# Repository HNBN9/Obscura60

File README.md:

# Obscura60
first keyboard build 60% wireless

Colored By -<br>
Mr.Finishing Surfacer 1500 Black<br>
Tamiya TS81 - top<br>
Tamiya TS55 - bottom<br>

Keycaps - 日当午GMK Prussian Alert普鲁(ordered 1 more 3u spacebar)<br>

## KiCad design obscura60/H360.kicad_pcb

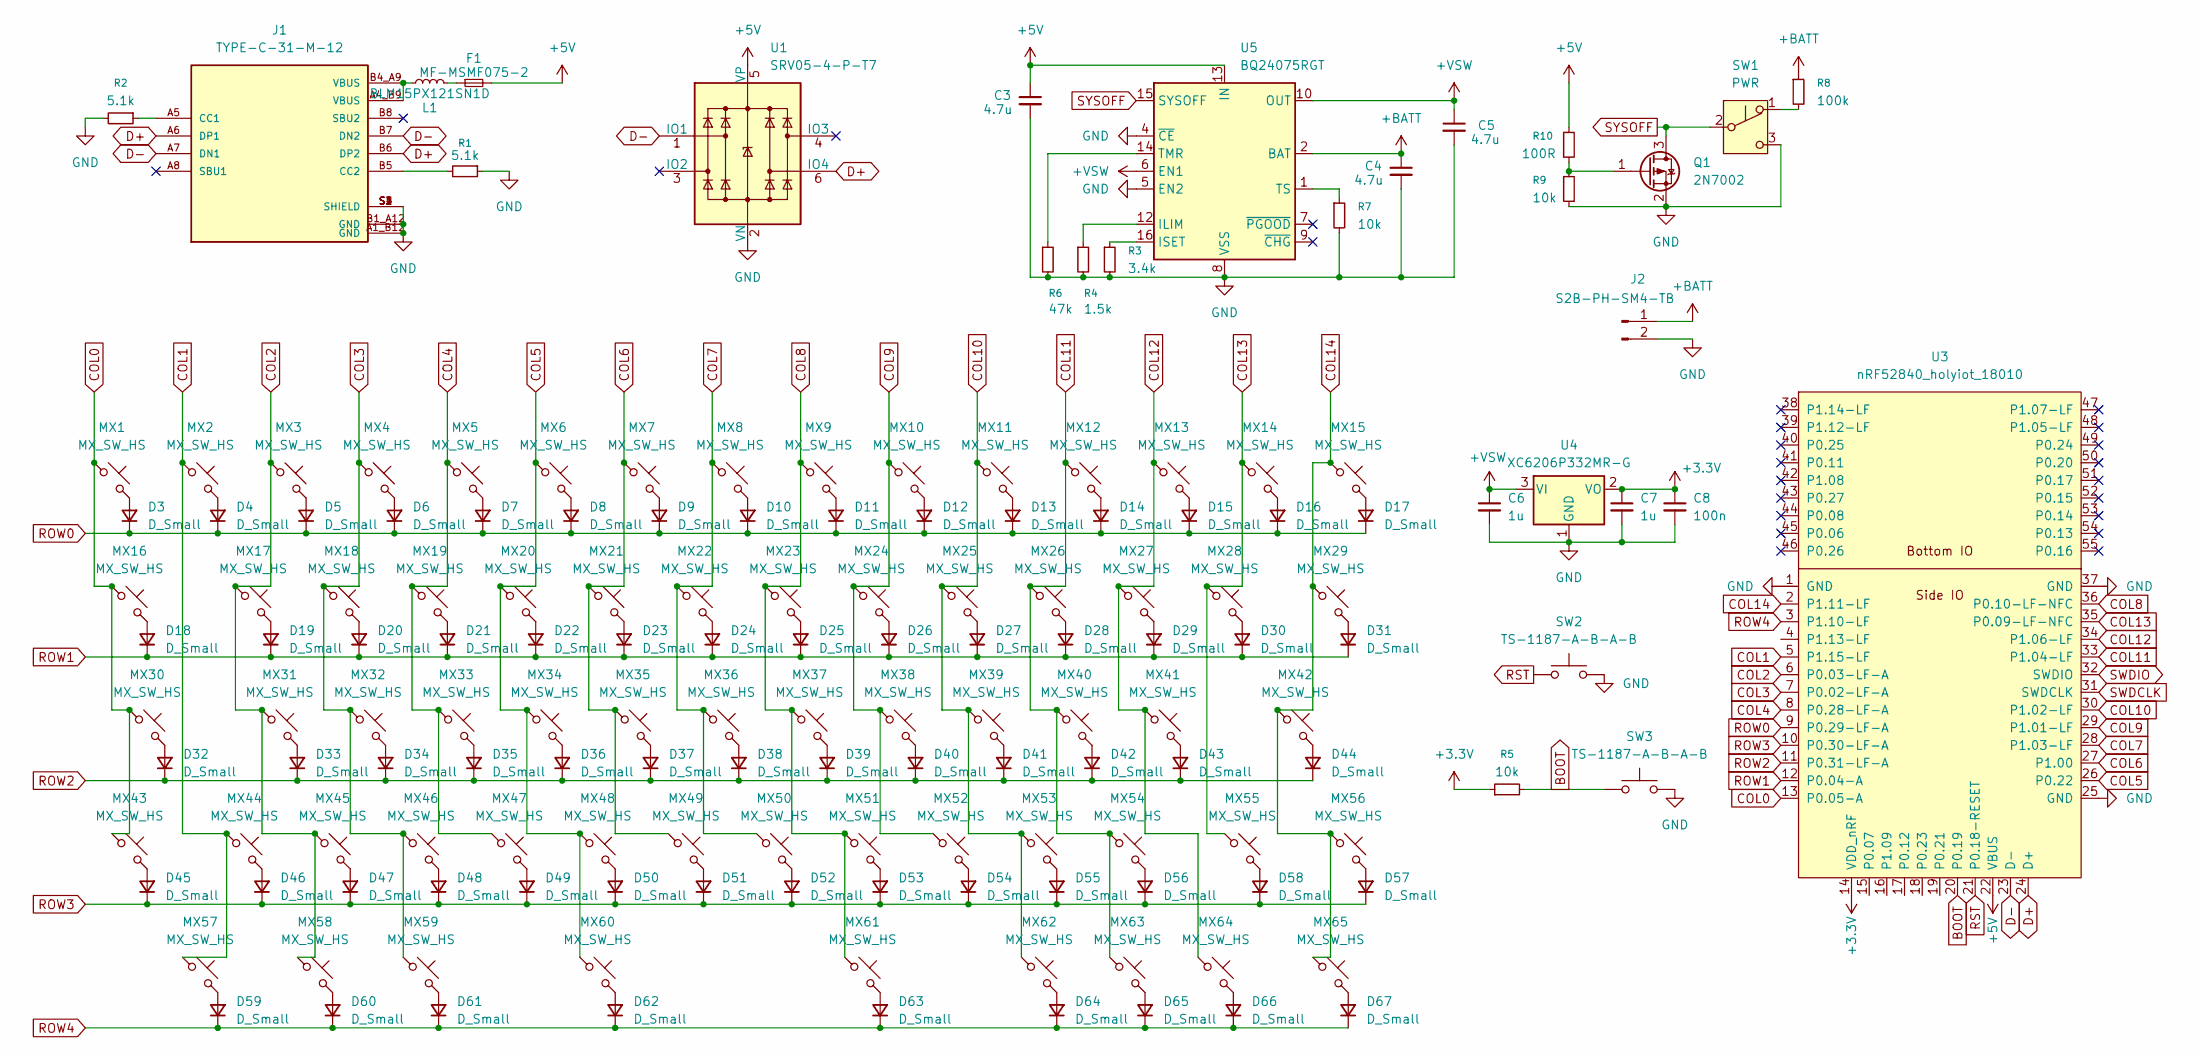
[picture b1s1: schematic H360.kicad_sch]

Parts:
C3, C4, C5: 4.7u; C_0603_1608Metric
C6, C7: 1u; C_1206_3216Metric
C8: 100n; C_0402_1005Metric
D3, D4, D5, D6, D7, D8, D9, D10, D11, D12, D13, D14, D15, D16, D17, D18, D19, D20, D21, D22, D23, D24, D25, D26, D27, D28, D29, D30, D31, D32, D33, D34, D35, D36, D37, D38, D39, D40, D41, D42, D43, D44, D45, D46, D47, D48, D49, D50, D51, D52, D53, D54, D55, D56, D57, D58, D59, D60, D61, D62, D63, D64, D65, D66, D67: D_Small; D_SOD-123
F1: MF-MSMF075-2; R_1812_4532Metric
J1: TYPE-C-31-M-12; HRO_TYPE-C-31-M-12; PARTREV 2020.12.08
J2: S2B-PH-SM4-TB; JST_PH_S2B-PH-SM4-TB_1x02-1MP_P2.00mm_Horizontal
L1: BLM15PX121SN1D; L_0402_1005Metric
MX1, MX2, MX3, MX4, MX5, MX6, MX7, MX8, MX9, MX10, MX11, MX12, MX13, MX14, MX15, MX16, MX17, MX18, MX19, MX20, MX21, MX22, MX23, MX24, MX25, MX26, MX27, MX28, MX29, MX30, MX31, MX32, MX33, MX34, MX35, MX36, MX37, MX38, MX39, MX40, MX41, MX42, MX43, MX44, MX45, MX46, MX47, MX48, MX49, MX50, MX51, MX52, MX53, MX54, MX55, MX56, MX57, MX58, MX59, MX60, MX61, MX62, MX63, MX64, MX65: MX_SW_HS; SW_MX_HS_CPG151101S11_1u
Q1: 2N7002; SOT-23
R1, R2: 5.1k; R_0402_1005Metric
R3: 3.4k; R_0603_1608Metric
R4: 1.5k; R_0402_1005Metric
R5, R7, R9: 10k; R_0402_1005Metric
R6: 47k; R_0402_1005Metric
R8: 100k; R_0402_1005Metric
R10: 100R; R_0402_1005Metric
SW1: PWR; SW_SPDT_CK_JS102011SAQN
SW2, SW3: TS-1187-A-B-A-B; SW_Push_1P1T_XKB_TS-1187A
U1: SRV05-4-P-T7; SOT-23-6
U3: nRF52840_holyiot_18010
U4: XC6206P332MR-G; SOT-23-3
U5: BQ24075RGT; VQFN-16-1EP_3x3mm_P0.5mm_EP1.6x1.6mm

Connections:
+3.3V: C7.1, C8.1, R5.1, U3.14 (VDD_nRF), U4.2 (VO)
+5V: C3.1, F1.2, R10.1, U1.5 (VP), U3.22 (VBUS), U5.13 (IN)
+BATT: C4.1, J2.1, R8.1, U5.2 (BAT), U5.3 (BAT)
+VSW: C5.1, C6.1, U4.3 (VI), U5.6 (EN1), U5.10 (OUT), U5.11 (OUT)
BOOT: R5.2, SW3.1, U3.20 (P0.19)
COL0: MX1.1, MX16.1, MX30.1, MX43.1, U3.13 (P0.05-A)
COL1: MX2.1, MX44.1, MX57.1, U3.5 (P1.15-LF)
COL2: MX3.1, MX17.1, MX31.1, MX45.1, MX58.1, U3.6 (P0.03-LF-A)
COL3: MX4.1, MX18.1, MX32.1, MX46.1, MX59.1, U3.7 (P0.02-LF-A)
COL4: MX5.1, MX19.1, MX33.1, MX47.1, U3.8 (P0.28-LF-A)
COL5: MX6.1, MX20.1, MX34.1, MX48.1, MX60.1, U3.26 (P0.22)
COL6: MX7.1, MX21.1, MX35.1, MX49.1, U3.27 (P1.00)
COL7: MX8.1, MX22.1, MX36.1, MX50.1, U3.28 (P1.03-LF)
COL8: MX9.1, MX23.1, MX37.1, MX51.1, MX61.1, U3.36 (P0.10-LF-NFC)
COL9: MX10.1, MX24.1, MX38.1, MX52.1, U3.29 (P1.01-LF)
COL10: MX11.1, MX25.1, MX39.1, MX53.1, MX62.1, U3.30 (P1.02-LF)
COL11: MX12.1, MX26.1, MX40.1, MX54.1, MX63.1, U3.33 (P1.04-LF)
COL12: MX13.1, MX27.1, MX41.1, MX64.1, U3.34 (P1.06-LF)
COL13: MX14.1, MX28.1, MX55.1, U3.35 (P0.09-LF-NFC)
COL14: MX15.1, MX29.1, MX42.1, MX56.1, MX65.1, U3.2 (P1.11-LF)
D+: J1.A6 (DP1), J1.B6 (DP2), U1.6 (IO4), U3.24 (D+)
D-: J1.A7 (DN1), J1.B7 (DN2), U1.1 (IO1), U3.23 (D-)
GND: C3.2, C4.2, C5.2, C6.2, C7.2, C8.2, J1.A1_B12 (GND), J1.B1_A12 (GND), J1.S1 (SHIELD), J1.S2 (SHIELD), J1.S3 (SHIELD), J1.S4 (SHIELD), J2.2, Q1.2 (S), R1.1, R2.2, R3.2, R4.2, R6.2, R7.2, R9.2, SW1.3 (C), SW2.2, SW3.2, U1.2 (VN), U3.1 (GND), U3.25 (GND), U3.37 (GND), U4.1 (GND), U5.4 (~CE), U5.5 (EN2), U5.8 (VSS), U5.17 (VSS)
unnamed: D3.2 (A), MX1.2
unnamed: D4.2 (A), MX2.2
unnamed: D5.2 (A), MX3.2
unnamed: D6.2 (A), MX4.2
unnamed: D7.2 (A), MX5.2
unnamed: D8.2 (A), MX6.2
unnamed: D9.2 (A), MX7.2
unnamed: D10.2 (A), MX8.2
unnamed: D11.2 (A), MX9.2
unnamed: D12.2 (A), MX10.2
unnamed: D13.2 (A), MX11.2
unnamed: D14.2 (A), MX12.2
unnamed: D15.2 (A), MX13.2
unnamed: D16.2 (A), MX14.2
unnamed: D17.2 (A), MX15.2
unnamed: D18.2 (A), MX16.2
unnamed: D19.2 (A), MX17.2
unnamed: D20.2 (A), MX18.2
unnamed: D21.2 (A), MX19.2
unnamed: D22.2 (A), MX20.2
unnamed: D23.2 (A), MX21.2
unnamed: D24.2 (A), MX22.2
unnamed: D25.2 (A), MX23.2
unnamed: D26.2 (A), MX24.2
unnamed: D27.2 (A), MX25.2
unnamed: D28.2 (A), MX26.2
unnamed: D29.2 (A), MX27.2
unnamed: D30.2 (A), MX28.2
unnamed: D31.2 (A), MX29.2
unnamed: D32.2 (A), MX30.2
unnamed: D33.2 (A), MX31.2
unnamed: D34.2 (A), MX32.2
unnamed: D35.2 (A), MX33.2
unnamed: D36.2 (A), MX34.2
unnamed: D37.2 (A), MX35.2
unnamed: D38.2 (A), MX36.2
unnamed: D39.2 (A), MX37.2
unnamed: D40.2 (A), MX38.2
unnamed: D41.2 (A), MX39.2
unnamed: D42.2 (A), MX40.2
unnamed: D43.2 (A), MX41.2
unnamed: D44.2 (A), MX42.2
unnamed: D45.2 (A), MX43.2
unnamed: D46.2 (A), MX44.2
unnamed: D47.2 (A), MX45.2
unnamed: D48.2 (A), MX46.2
unnamed: D49.2 (A), MX47.2
unnamed: D50.2 (A), MX48.2
unnamed: D51.2 (A), MX49.2
unnamed: D52.2 (A), MX50.2
unnamed: D53.2 (A), MX51.2
unnamed: D54.2 (A), MX52.2
unnamed: D55.2 (A), MX53.2
unnamed: D56.2 (A), MX54.2
unnamed: D57.2 (A), MX56.2
unnamed: D58.2 (A), MX55.2
unnamed: D59.2 (A), MX57.2
unnamed: D60.2 (A), MX58.2
unnamed: D61.2 (A), MX59.2
unnamed: D62.2 (A), MX60.2
unnamed: D63.2 (A), MX61.2
unnamed: D64.2 (A), MX62.2
unnamed: D65.2 (A), MX63.2
unnamed: D66.2 (A), MX64.2
unnamed: D67.2 (A), MX65.2
unnamed: F1.1, L1.2
unnamed: J1.A5 (CC1), R2.1
unnamed: J1.B5 (CC2), R1.2
unnamed: J1.A4_B9 (VBUS), J1.B4_A9 (VBUS), L1.1
unnamed: Q1.1 (G), R9.1, R10.2
unnamed: R8.2, SW1.1 (A)
unnamed: R4.1, U5.12 (ILIM)
unnamed: R3.1, U5.16 (ISET)
unnamed: R6.1, U5.14 (TMR)
unnamed: R7.1, U5.1 (TS)
ROW0: D3.1 (K), D4.1 (K), D5.1 (K), D6.1 (K), D7.1 (K), D8.1 (K), D9.1 (K), D10.1 (K), D11.1 (K), D12.1 (K), D13.1 (K), D14.1 (K), D15.1 (K), D16.1 (K), D17.1 (K), U3.9 (P0.29-LF-A)
ROW1: D18.1 (K), D19.1 (K), D20.1 (K), D21.1 (K), D22.1 (K), D23.1 (K), D24.1 (K), D25.1 (K), D26.1 (K), D27.1 (K), D28.1 (K), D29.1 (K), D30.1 (K), D31.1 (K), U3.12 (P0.04-A)
ROW2: D32.1 (K), D33.1 (K), D34.1 (K), D35.1 (K), D36.1 (K), D37.1 (K), D38.1 (K), D39.1 (K), D40.1 (K), D41.1 (K), D42.1 (K), D43.1 (K), D44.1 (K), U3.11 (P0.31-LF-A)
ROW3: D45.1 (K), D46.1 (K), D47.1 (K), D48.1 (K), D49.1 (K), D50.1 (K), D51.1 (K), D52.1 (K), D53.1 (K), D54.1 (K), D55.1 (K), D56.1 (K), D57.1 (K), D58.1 (K), U3.10 (P0.30-LF-A)
ROW4: D59.1 (K), D60.1 (K), D61.1 (K), D62.1 (K), D63.1 (K), D64.1 (K), D65.1 (K), D66.1 (K), D67.1 (K), U3.3 (P1.10-LF)
RST: SW2.1, U3.21 (P0.18-RESET)
SWDCLK: U3.31 (SWDCLK)
SWDIO: U3.32 (SWDIO)
SYSOFF: Q1.3 (D), SW1.2 (B), U5.15 (SYSOFF)

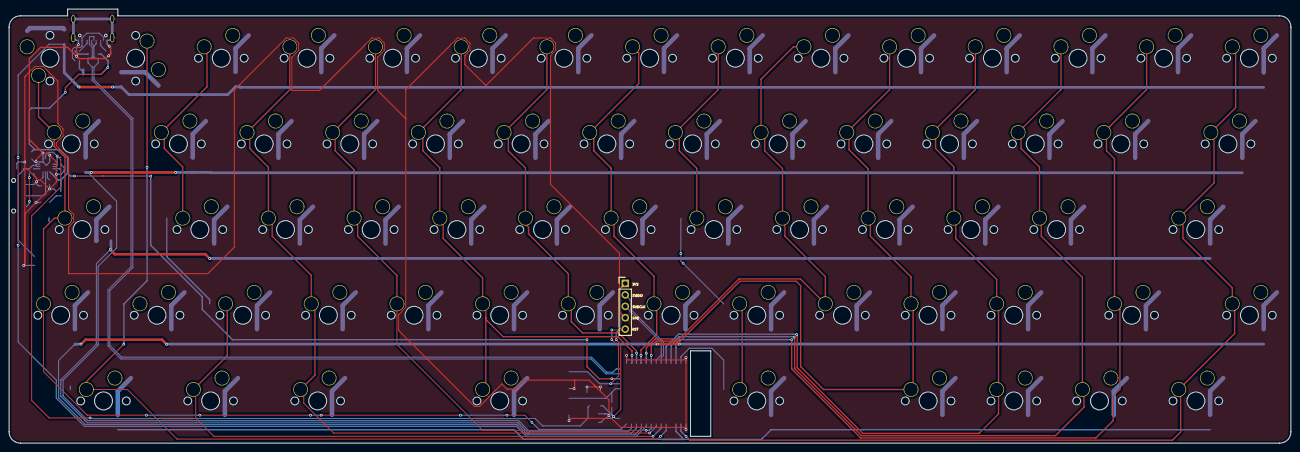
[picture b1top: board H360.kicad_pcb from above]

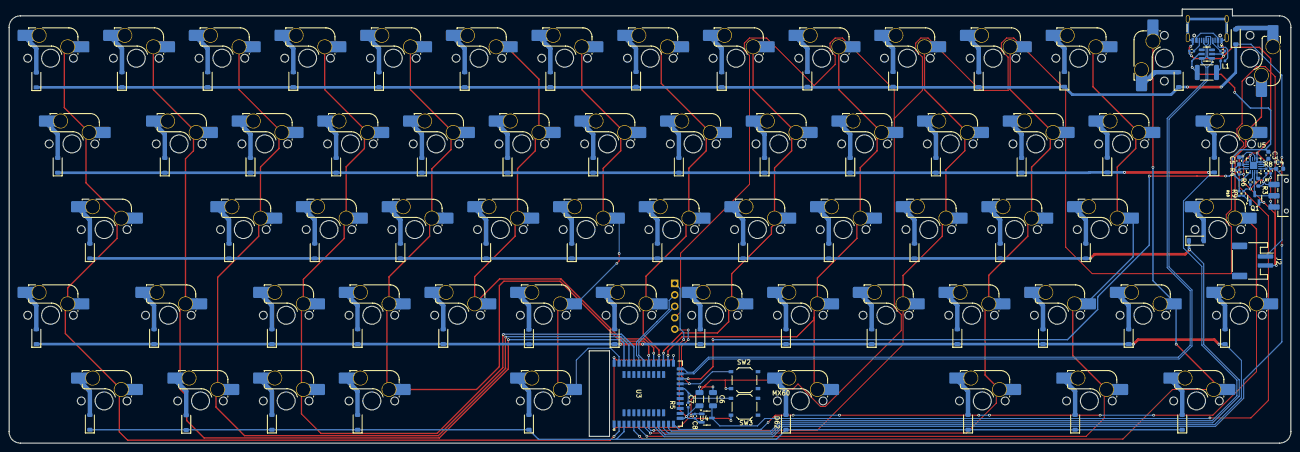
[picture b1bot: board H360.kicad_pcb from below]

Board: 2 copper layers, 285.0 x 96.5 mm, 158 parts (158 on the bottom side), 105 nets.

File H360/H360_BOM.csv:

Comment,Reference,Footprint,LCSC Part Number
4.7u,"C3,C4,C5",Capacitor_SMD:C_0603_1608Metric,C19666
1u,"C6,C7",Capacitor_SMD:C_1206_3216Metric,C15850
100n,C8,Capacitor_SMD:C_0402_1005Metric,C1525
D_Small,"D3,D4,D5,D6,D7,D8,D9,D10,D11,D12,D13,D14,D15,D16,D17,D18,D19,D20,D21,D22,D23,D24,D25,D26,D27,D28,D29,D30,D31,D32,D33,D34,D35,D36,D37,D38,D39,D40,D41,D42,D43,D44,D45,D46,D47,D48,D49,D50,D51,D52,D53,D54,D55,D56,D57,D58,D59,D60,D61,D62,D63,D64,D65,D66,D67",Diode_SMD:D_SOD-123,C81598
MF-MSMF075-2,F1,Resistor_SMD:R_1812_4532Metric,C84140
BLM15PX121SN1D,L1,Inductor_SMD:L_0402_1005Metric,C88970
2N7002,Q1,Package_TO_SOT_SMD:SOT-23,C8545
5.1k,"R1,R2",Resistor_SMD:R_0402_1005Metric,C25905
3.4k,R3,Resistor_SMD:R_0603_1608Metric,C25804
1.5k,R4,Resistor_SMD:R_0402_1005Metric,C25867
10k,"R5,R7,R8,R9",Resistor_SMD:R_0402_1005Metric,C25744
47k,R6,Resistor_SMD:R_0402_1005Metric,C25792
100R,R10,Resistor_SMD:R_0402_1005Metric,C25076
TS-1187-A-B-A-B,"SW2,SW3",Button_Switch_SMD:SW_Push_1P1T_XKB_TS-1187A,C318884
SRV05-4-P-T7,U1,Package_TO_SOT_SMD:SOT-23-6,C85364
XC6206P332MR-G,U4,Package_TO_SOT_SMD:SOT-23-3,C5446
BQ24075RGT,U5,Package_DFN_QFN:VQFN-16-1EP_3x3mm_P0.5mm_EP1.6x1.6mm,C15464

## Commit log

2025-04-25 Initialize project
2025-04-28 sch updat4e
2025-05-03 sch update
2025-05-03 charger update
2025-05-11 first final
2025-05-11 3d update
2025-05-11 3d re update
2025-05-11 small fix
2025-05-11 fixes
2025-05-11 fixed routing
2025-05-11 routing fixed
2025-05-14 else
2025-05-16 05.16
2025-06-27 change name
2025-07-02 README.md 업데이트
2025-09-19 stl files uploaded
2025-09-19 image
